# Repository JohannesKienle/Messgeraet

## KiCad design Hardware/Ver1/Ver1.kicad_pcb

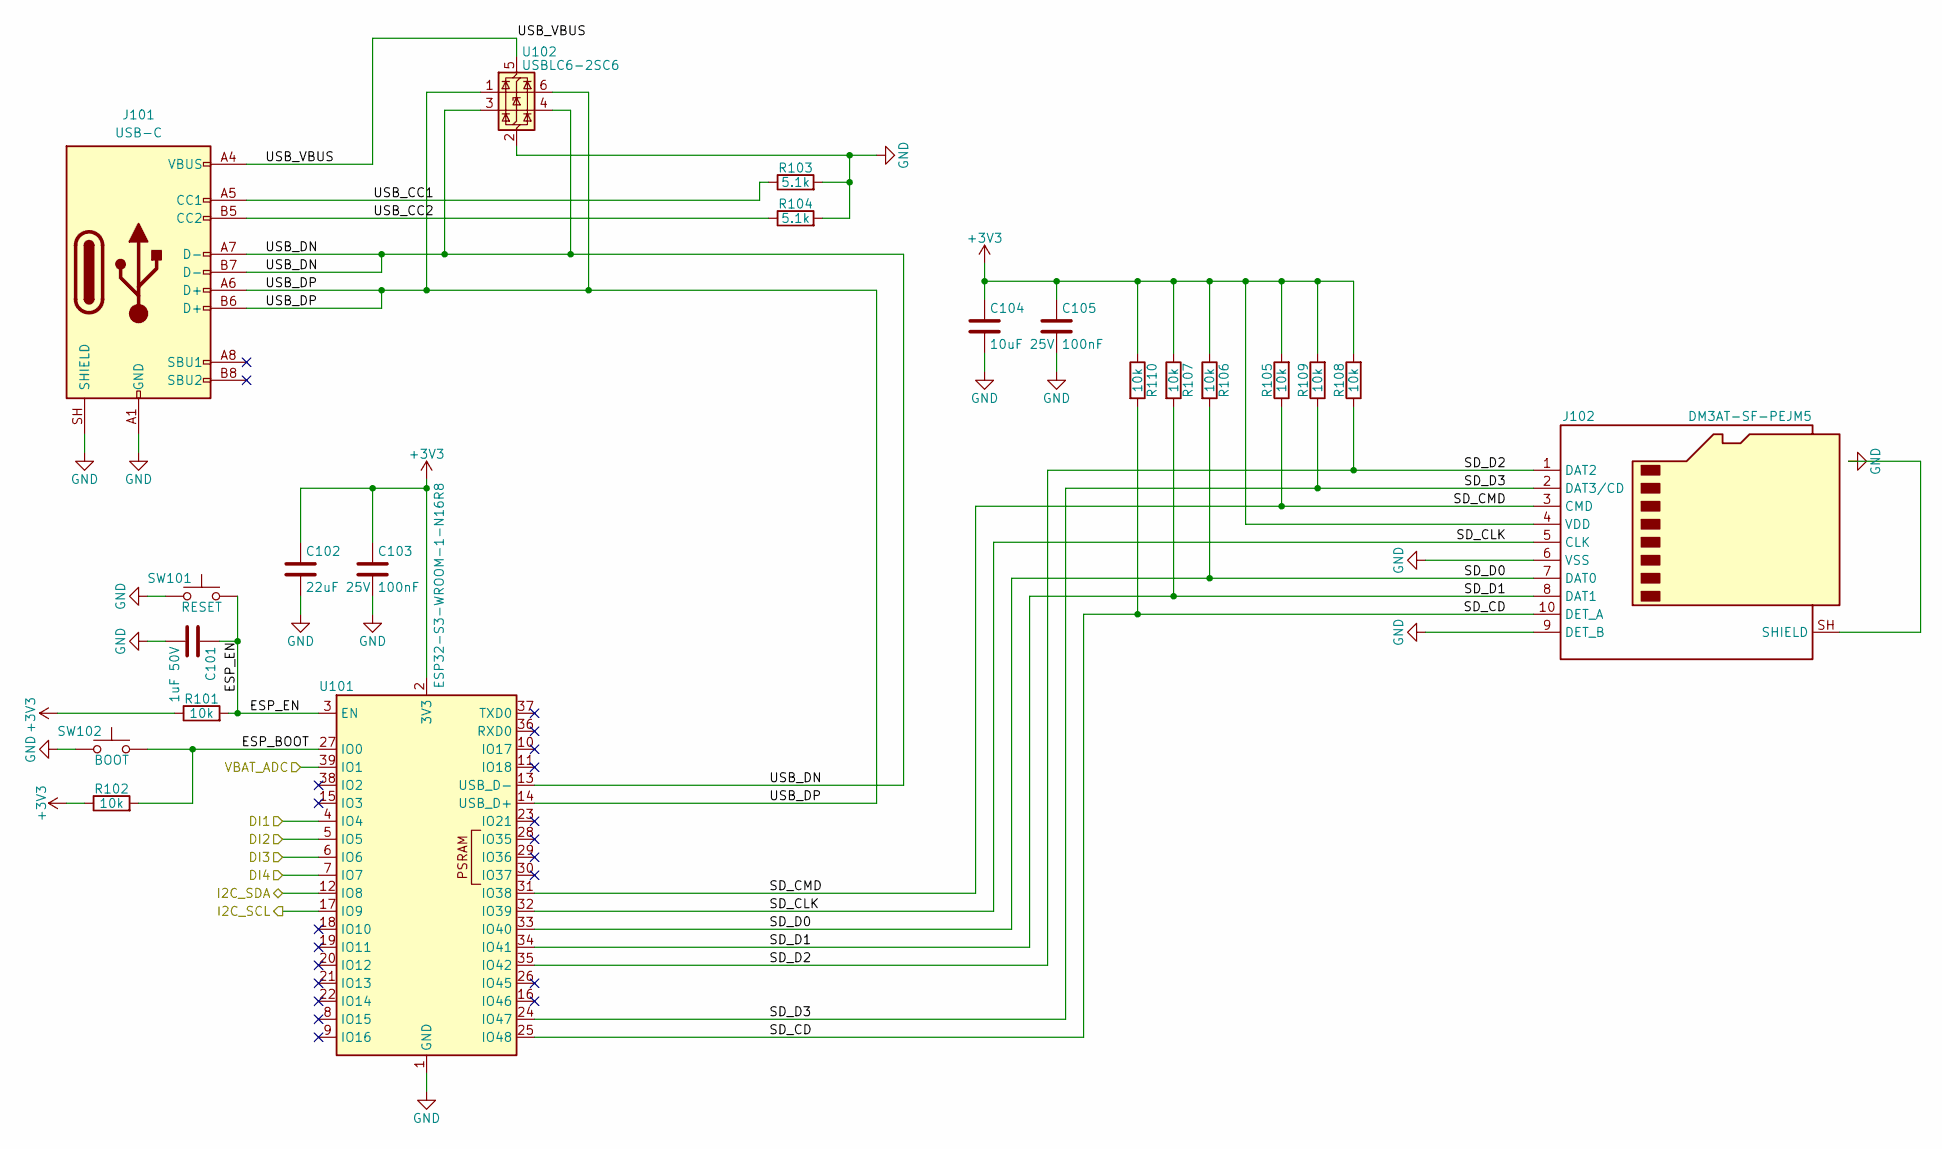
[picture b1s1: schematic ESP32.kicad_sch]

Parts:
C101: 1uF 50V; C_0805_2012Metric; MPN CL21B105KBFNNNE; LCSC C28323
C102: 22uF 25V; C_0805_2012Metric; MPN CL21A226MAQNNNE; LCSC C45783
C103, C105: 100nF; C_0805_2012Metric; MPN CC0805KRX7R9BB104; LCSC C49678
C104: 10uF 25V; C_0805_2012Metric; MPN CL21A106KAYNNNE; LCSC C15850
J101: USB-C; USB_C_Receptacle_HRO_TYPE-C-31-M-12; MPN TYPE-C-31-M-12; LCSC C165948
J102: DM3AT-SF-PEJM5; microSD_HC_Hirose_DM3AT-SF-PEJM5; MPN DM3AT-SF-PEJM5; LCSC C114218
R101, R102, R105, R106, R107, R108, R109, R110: 10k; R_0805_2012Metric; MPN 0805W8F1002T5E; LCSC C17414
R103, R104: 5.1k; R_0805_2012Metric; MPN 0805W8F5101T5E; LCSC C27834
SW101: RESET; SW_Push_1P1T_XKB_TS-1187A; MPN TS-1187A-B-A-B; LCSC C318884
SW102: BOOT; SW_Push_1P1T_XKB_TS-1187A; MPN TS-1187A-B-A-B; LCSC C318884
U101: ESP32-S3-WROOM-1-N16R8; ESP32-S3-WROOM-1; MPN ESP32-S3-WROOM-1-N16R8; LCSC C2913202
U102: USBLC6-2SC6; SOT-23-6; MPN USBLC6-2SC6; LCSC C2687116

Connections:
+3V3: C102.1, C103.1, C104.1, C105.1, J102.4 (VDD), R101.1, R102.1, R105.2, R106.1, R107.1, R108.2, R109.2, R110.1, U101.2 (3V3); also elsewhere on the board
/Analogeingänge/I2C_SCL: U101.17 (IO9); also elsewhere on the board
/Analogeingänge/I2C_SDA: U101.12 (IO8); also elsewhere on the board
/Digitaleingänge/DI1: U101.4 (IO4); also elsewhere on the board
/Digitaleingänge/DI2: U101.5 (IO5); also elsewhere on the board
/Digitaleingänge/DI3: U101.6 (IO6); also elsewhere on the board
/Digitaleingänge/DI4: U101.7 (IO7); also elsewhere on the board
/ESP32/ESP_BOOT: R102.2, SW102.1, U101.27 (IO0)
/ESP32/ESP_EN: C101.1, R101.2, SW101.1, U101.3 (EN)
/ESP32/SD_CD: J102.10 (DET_A), R110.2, U101.25 (IO48)
/ESP32/SD_CLK: J102.5 (CLK), U101.32 (IO39)
/ESP32/SD_CMD: J102.3 (CMD), R105.1, U101.31 (IO38)
/ESP32/SD_D0: J102.7 (DAT0), R106.2, U101.33 (IO40)
/ESP32/SD_D1: J102.8 (DAT1), R107.2, U101.34 (IO41)
/ESP32/SD_D2: J102.1 (DAT2), R108.1, U101.35 (IO42)
/ESP32/SD_D3: J102.2 (DAT3/CD), R109.1, U101.24 (IO47)
/ESP32/USB_CC1: J101.A5 (CC1), R103.1
/ESP32/USB_CC2: J101.B5 (CC2), R104.1
/ESP32/USB_DN: J101.A7 (D-), J101.B7 (D-), U101.13 (USB_D-), U102.3 (I/O2), U102.4 (I/O2)
/ESP32/USB_DP: J101.A6 (D+), J101.B6 (D+), U101.14 (USB_D+), U102.1 (I/O1), U102.6 (I/O1)
/ESP32/USB_VBUS: J101.A4 (VBUS), J101.A9 (VBUS), J101.B4 (VBUS), J101.B9 (VBUS), U102.5 (VBUS)
/Versorgung/VBAT_ADC: U101.39 (IO1); also elsewhere on the board

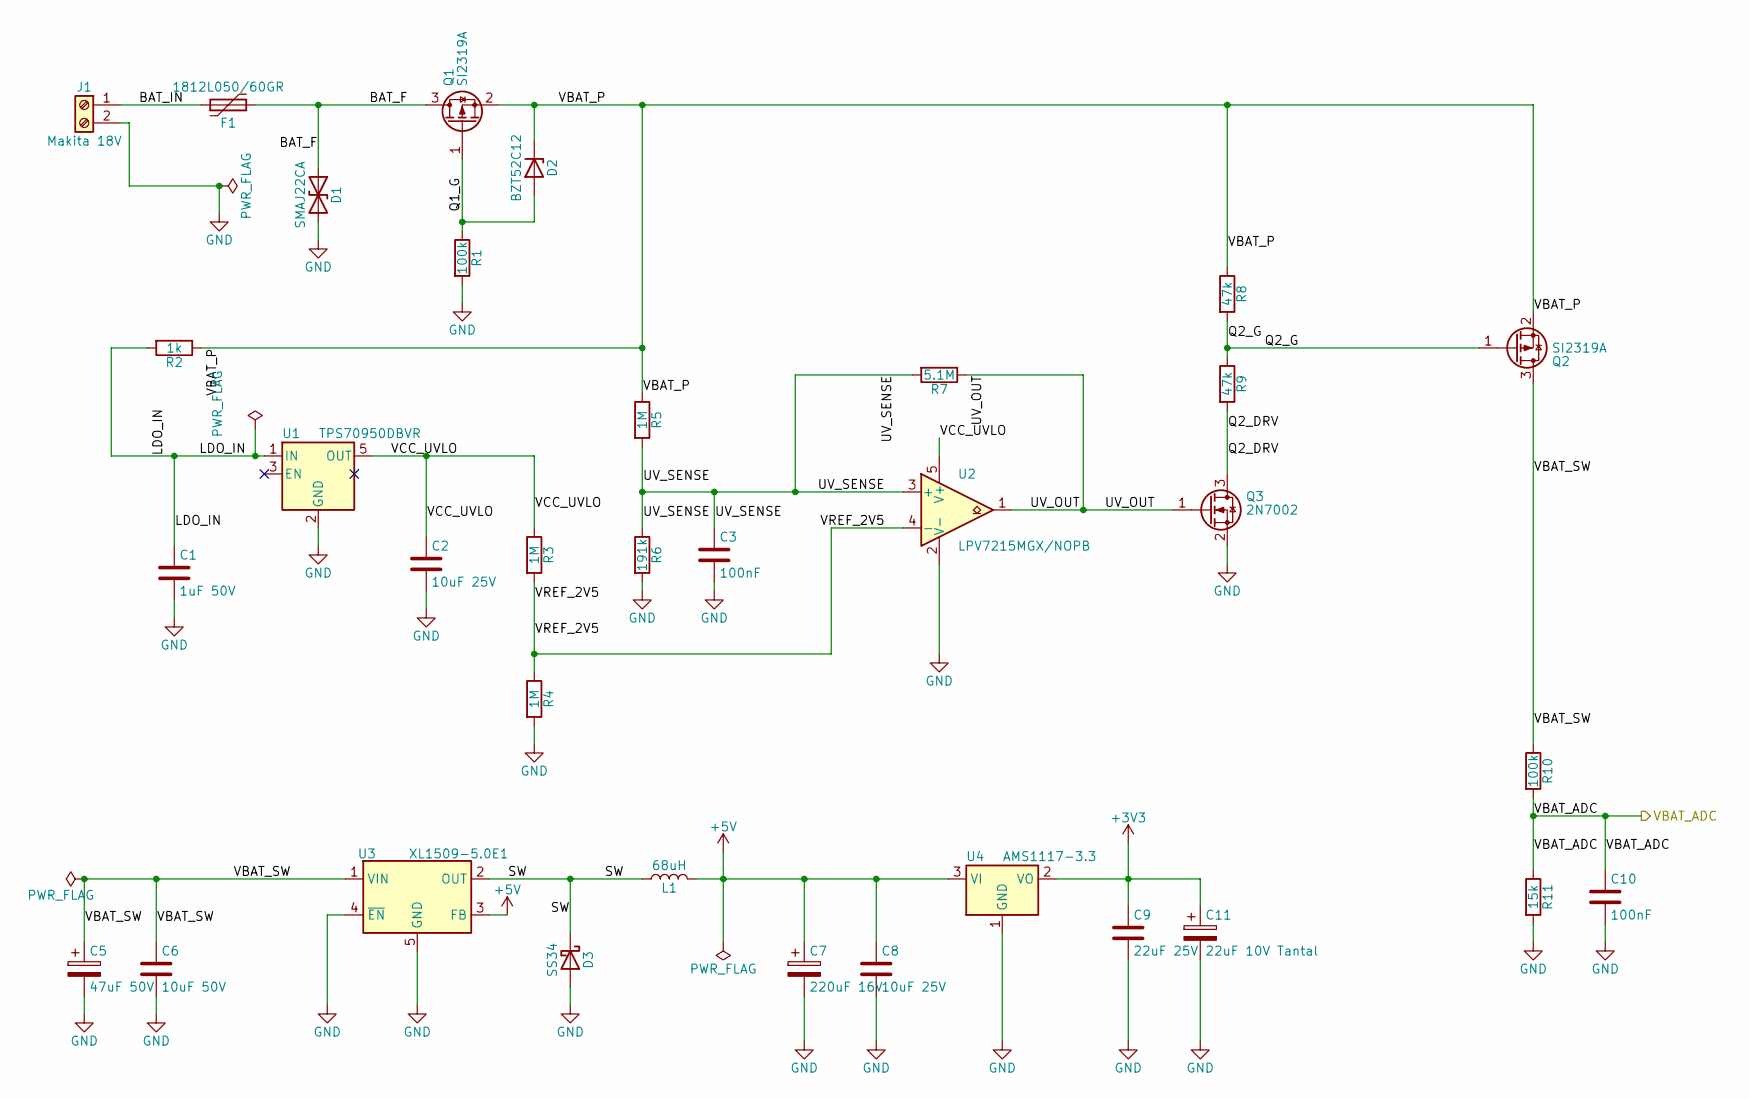
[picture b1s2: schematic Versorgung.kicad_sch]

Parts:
C1: 1uF 50V; C_0805_2012Metric; MPN CL21B105KBFNNNE; LCSC C28323
C2, C8: 10uF 25V; C_0805_2012Metric; MPN CL21A106KAYNNNE; LCSC C15850
C3, C10: 100nF; C_0805_2012Metric; MPN CC0805KRX7R9BB104; LCSC C49678
C5: 47uF 50V; CP_Radial_D6.3mm_P2.50mm; MPN ERM1HM470E11OT; LCSC C106605
C6: 10uF 50V; C_0805_2012Metric; MPN GRM21BR61H106KE43L; LCSC C440198
C7: 220uF 16V; CP_Elec_6.3x7.7; MPN EEEFK1C221P; LCSC C178534
C9: 22uF 25V; C_0805_2012Metric; MPN CL21A226MAQNNNE; LCSC C45783
C11: 22uF 10V Tantal; CP_EIA-3528-21_Kemet-B; MPN TAJB226K010RNJ; LCSC C7198
D1: SMAJ22CA; D_SMA; MPN SMAJ22CA; LCSC C113961
D2: BZT52C12; D_SOD-123; MPN BZT52C12; LCSC C43491
D3: SS34; D_SMA; MPN SS34; LCSC C8678
F1: 1812L050/60GR; Fuse_1812_4532Metric; MPN 1812L050/60GR; LCSC C19078719
J1: Makita 18V; TestPoint_2Pads_Pitch5.08mm_Drill1.3mm
L1: 68uH; L_Sunlord_SWPA8040S; MPN SWPA8040S680MT; LCSC C36418
Q1, Q2: SI2319A; SOT-23; MPN SI2319A; LCSC C545576
Q3: 2N7002; SOT-23; MPN 2N7002; LCSC C8545
R1, R10: 100k; R_0805_2012Metric; MPN 0805W8F1003T5E; LCSC C149504
R2: 1k; R_0805_2012Metric; MPN 0805W8F1001T5E; LCSC C17513
R3, R4, R5: 1M; R_0805_2012Metric; MPN 0805W8F1004T5E; LCSC C17514
R6: 191k; R_0805_2012Metric; MPN 0805W8F1913T5E; LCSC C17511
R7: 5.1M; R_0805_2012Metric; MPN 0805W8F5104T5E; LCSC C26114
R8, R9: 47k; R_0805_2012Metric; MPN 0805W8F4702T5E; LCSC C17713
R11: 15k; R_0805_2012Metric; MPN 0805W8F1502T5E; LCSC C17475
U1: TPS70950DBVR; SOT-23-5; MPN TPS70950DBVR; LCSC C96028
U2: LPV7215MGX/NOPB; SOT-353_SC-70-5; MPN LPV7215MGX/NOPB; LCSC C2878861
U3: XL1509-5.0E1; SOIC-8_3.9x4.9mm_P1.27mm; MPN XL1509-5.0E1; LCSC C61063
U4: AMS1117-3.3; SOT-223-3_TabPin2; MPN AMS1117-3.3; LCSC C6186

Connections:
+3V3: C9.1, C11.1, U4.2 (VO); also elsewhere on the board
/Versorgung/BAT_F: D1.1 (A1), F1.2, Q1.3 (D)
/Versorgung/BAT_IN: F1.1, J1.1
/Versorgung/Q1_G: D2.2 (A), Q1.1 (G), R1.1
/Versorgung/Q2_DRV: Q3.3 (D), R9.2
/Versorgung/Q2_G: Q2.1 (G), R8.2, R9.1
/Versorgung/SW: D3.1 (K), L1.1, U3.2 (OUT)
/Versorgung/UV_OUT: Q3.1 (G), R7.1, U2.1
/Versorgung/UV_SENSE: C3.1, R5.2, R6.1, R7.2, U2.3 (+)
/Versorgung/VBAT_ADC: C10.1, R10.2, R11.1; also elsewhere on the board
/Versorgung/VBAT_P: D2.1 (K), Q1.2 (S), Q2.2 (S), R2.1, R5.1, R8.1
/Versorgung/VCC_UVLO: C2.1, R3.1, U1.5 (OUT), U2.5 (V+)
/Versorgung/VREF_2V5: R3.2, R4.1, U2.4 (-)

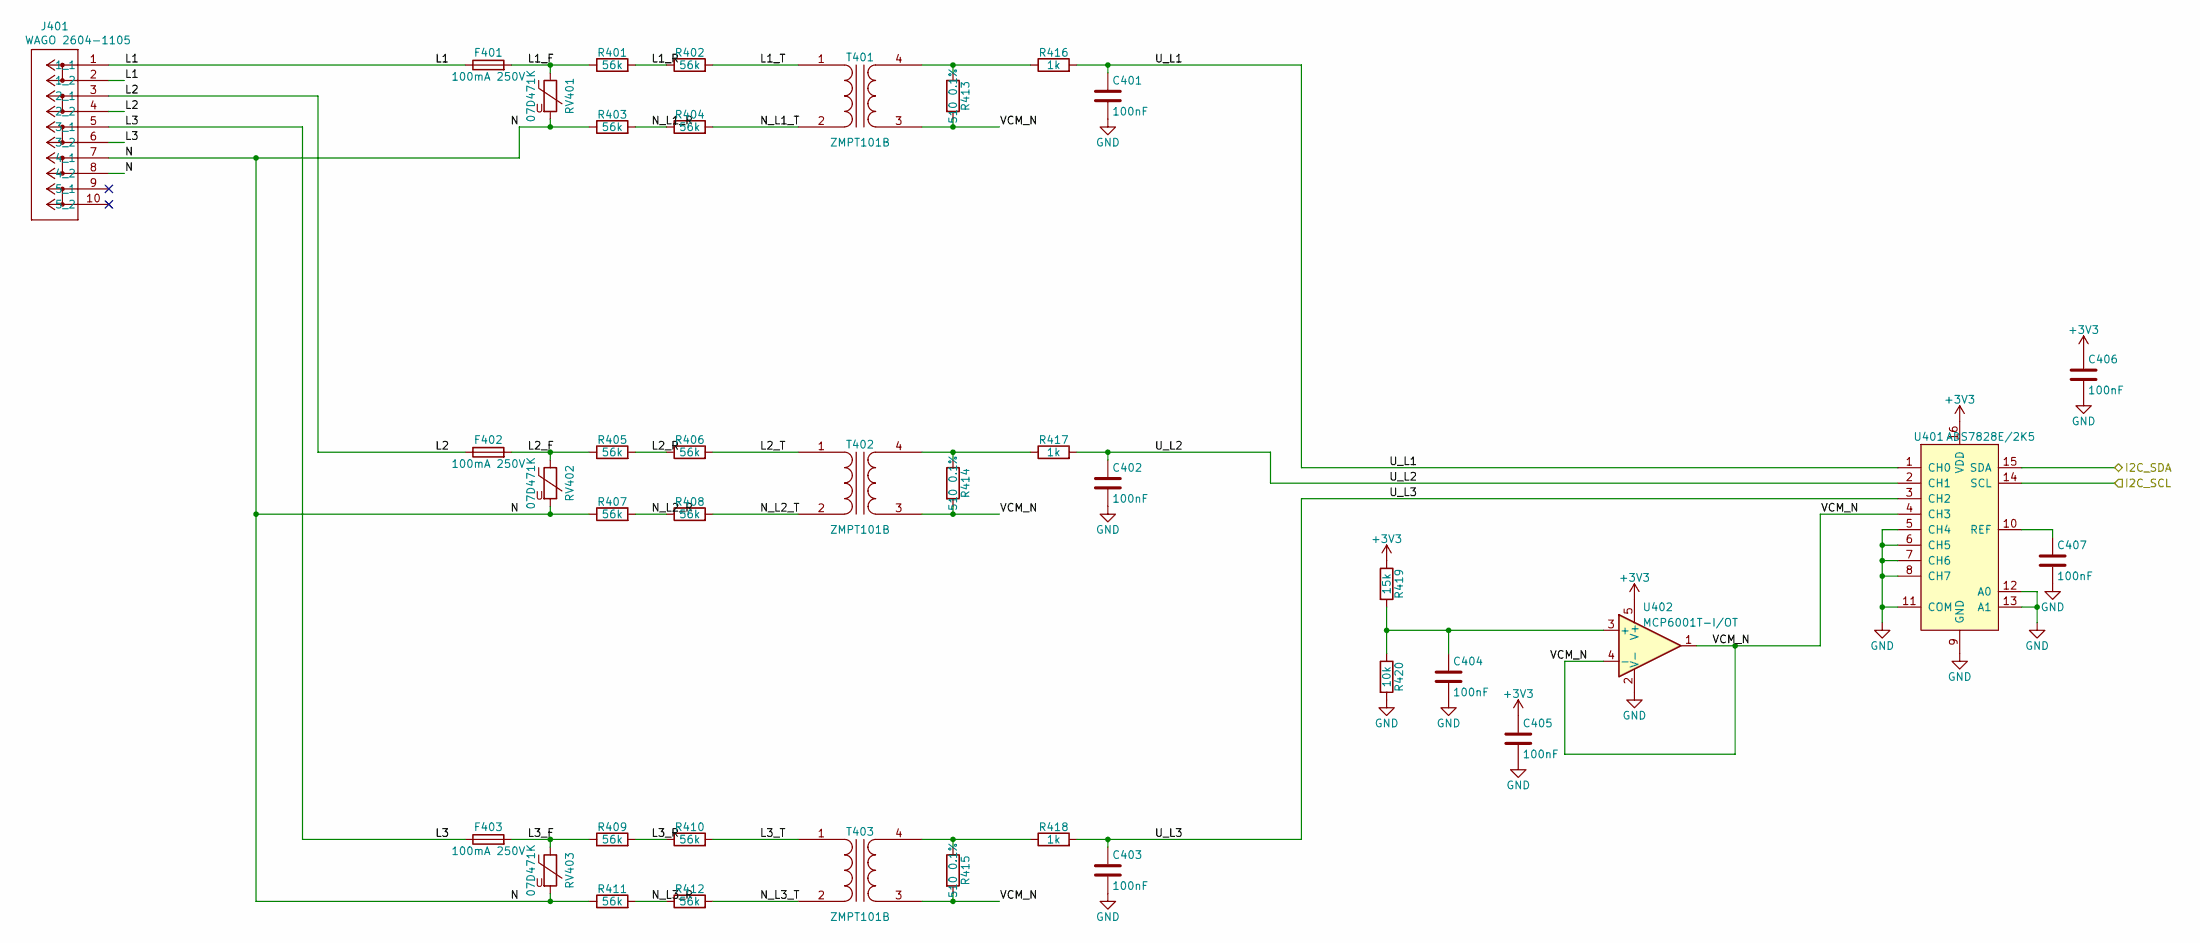
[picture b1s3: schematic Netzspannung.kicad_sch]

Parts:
C401, C402, C403, C404, C405, C406, C407: 100nF; C_0805_2012Metric; MPN CC0805KRX7R9BB104; LCSC C49678
F401, F402, F403: 100mA 250V; Fuse_2410_JDT_JFC2410; MPN JFC2410-0100FS; LCSC C48686858
J401: WAGO 2604-1105; CONN5_2604-1105_WAG; MPN WAGO 2604-1105
R401, R402, R403, R404, R405, R406, R407, R408, R409, R410, R411, R412: 56k; R_1206_3216Metric; MPN 1206W4F5602T5E; LCSC C18029
R413, R414, R415: 510 0.1%; R_0805_2012Metric; MPN RT0805BRD07510RL; LCSC C309660
R416, R417, R418: 1k; R_0805_2012Metric; MPN 0805W8F1001T5E; LCSC C17513
R419: 15k; R_0805_2012Metric; MPN 0805W8F1502T5E; LCSC C17475
R420: 10k; R_0805_2012Metric; MPN 0805W8F1002T5E; LCSC C17414
RV401, RV402, RV403: 07D471K; RV_Disc_D7mm_W3.4mm_P5mm; MPN 07D471K; LCSC C28756
T401, T402, T403: ZMPT101B; Transformer_Zeming_ZMPT101K; MPN ZMPT101B; LCSC C111858
U401: ADS7828E/2K5; TSSOP-16_4.4x5mm_P0.65mm; MPN ADS7828E/2K5; LCSC C701649
U402: MCP6001T-I/OT; SOT-23-5; MPN MCP6001T-I/OT; LCSC C116490

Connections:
+3V3: C405.1, C406.1, R419.1, U401.16 (VDD), U402.5 (V+); also elsewhere on the board
/Analogeingänge/I2C_SCL: U401.14 (SCL); also elsewhere on the board
/Analogeingänge/I2C_SDA: U401.15 (SDA); also elsewhere on the board
/Netzspannung/L1: F401.1, J401.1 (1_1), J401.2 (1_2)
/Netzspannung/L1_F: F401.2, R401.1, RV401.1
/Netzspannung/L1_R: R401.2, R402.1
/Netzspannung/L1_T: R402.2, T401.1 (AA)
/Netzspannung/L2: F402.1, J401.3 (2_1), J401.4 (2_2)
/Netzspannung/L2_F: F402.2, R405.1, RV402.1
/Netzspannung/L2_R: R405.2, R406.1
/Netzspannung/L2_T: R406.2, T402.1 (AA)
/Netzspannung/L3: F403.1, J401.5 (3_1), J401.6 (3_2)
/Netzspannung/L3_F: F403.2, R409.1, RV403.1
/Netzspannung/L3_R: R409.2, R410.1
/Netzspannung/L3_T: R410.2, T403.1 (AA)
/Netzspannung/N: J401.7 (4_1), J401.8 (4_2), R403.1, R407.1, R411.1, RV401.2, RV402.2, RV403.2
/Netzspannung/N_L1_R: R403.2, R404.1
/Netzspannung/N_L1_T: R404.2, T401.2 (AB)
/Netzspannung/N_L2_R: R407.2, R408.1
/Netzspannung/N_L2_T: R408.2, T402.2 (AB)
/Netzspannung/N_L3_R: R411.2, R412.1
/Netzspannung/N_L3_T: R412.2, T403.2 (AB)
/Netzspannung/U_L1: C401.1, R416.2, U401.1 (CH0)
/Netzspannung/U_L2: C402.1, R417.2, U401.2 (CH1)
/Netzspannung/U_L3: C403.1, R418.2, U401.3 (CH2)
/Netzspannung/VCM_N: R413.2, R414.2, R415.2, T401.3 (SA), T402.3 (SA), T403.3 (SA), U401.4 (CH3), U402.1, U402.4 (-)
unnamed: R413.1, R416.1, T401.4 (SB)
unnamed: R414.1, R417.1, T402.4 (SB)
unnamed: R415.1, R418.1, T403.4 (SB)
unnamed: C407.1, U401.10 (REF)
unnamed: C404.1, R419.2, R420.1, U402.3 (+)

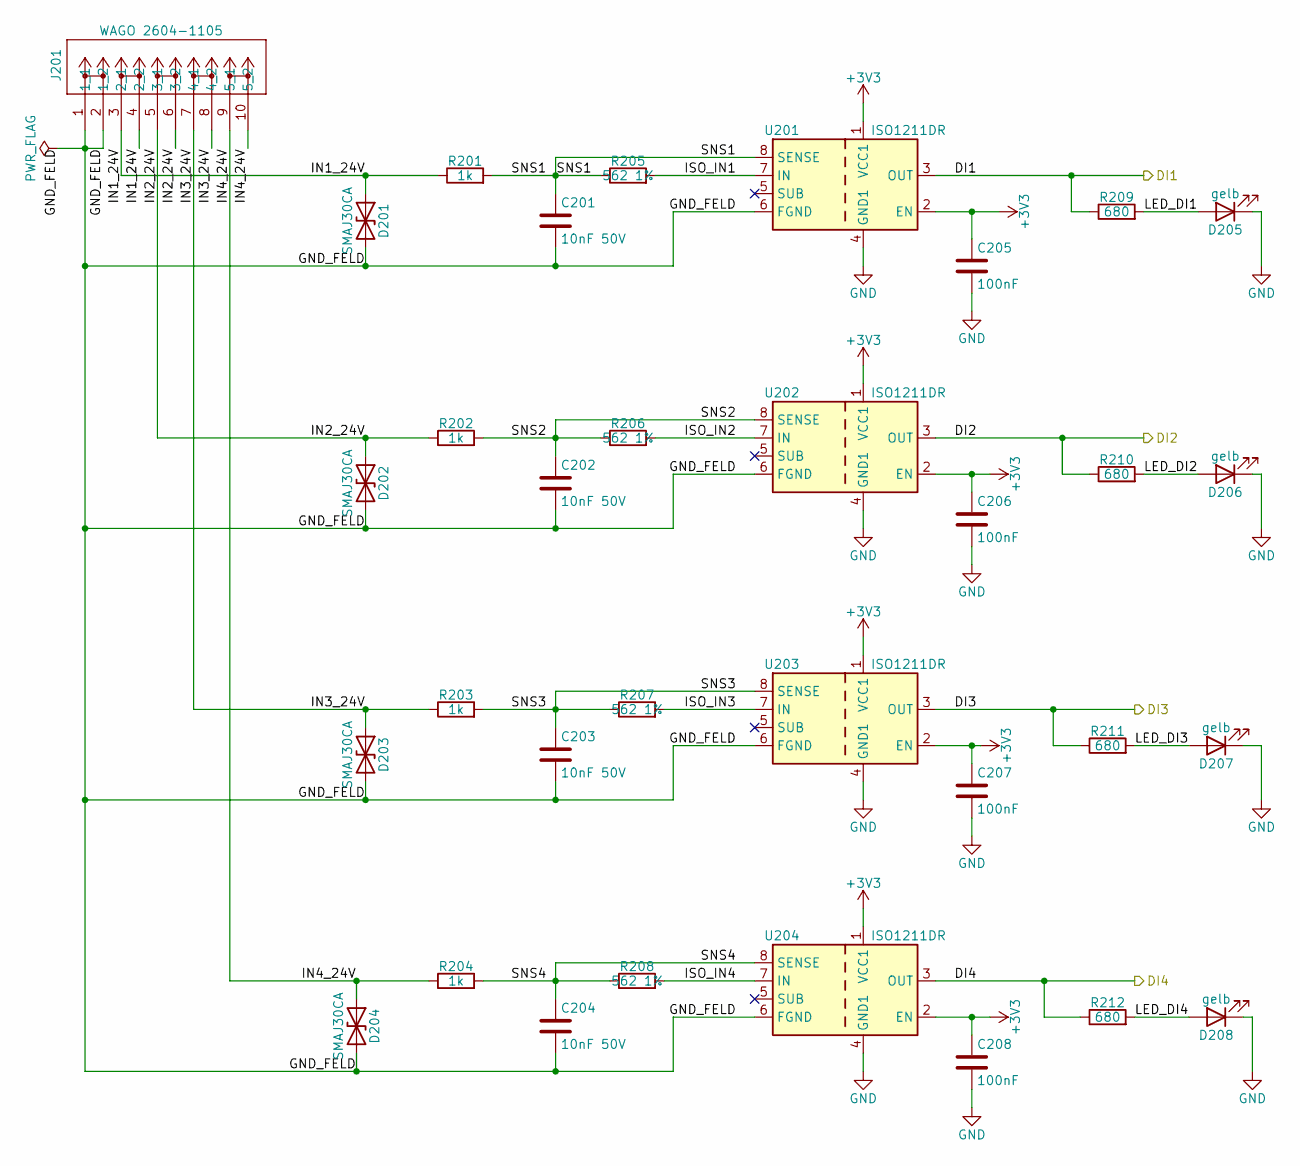
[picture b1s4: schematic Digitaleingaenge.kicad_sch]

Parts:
C201, C202, C203, C204: 10nF 50V; C_0805_2012Metric; MPN CL21B103KBANNNC; LCSC C1710
C205, C206, C207, C208: 100nF; C_0805_2012Metric; MPN CC0805KRX7R9BB104; LCSC C49678
D201, D202, D203, D204: SMAJ30CA; D_SMA; MPN SMAJ30CA; LCSC C83322
D205, D206, D207, D208: gelb; LED_0805_2012Metric; MPN KT-0805Y; LCSC C2296
J201: WAGO 2604-1105; CONN5_2604-1105_WAG; MPN WAGO 2604-1105
R201, R202, R203, R204: 1k; R_0805_2012Metric; MPN 0805W8F1001T5E; LCSC C17513
R205, R206, R207, R208: 562 1%; R_0805_2012Metric; MPN 0805W8F5620T5E; LCSC C17755
R209, R210, R211, R212: 680; R_0805_2012Metric; MPN 0805W8F6800T5E; LCSC C17798
U201, U202, U203, U204: ISO1211DR; SOIC-8_3.9x4.9mm_P1.27mm; MPN ISO1211DR; LCSC C2674102

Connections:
+3V3: C205.1, C206.1, C207.1, C208.1, U201.1 (VCC1), U201.2 (EN), U202.1 (VCC1), U202.2 (EN), U203.1 (VCC1), U203.2 (EN), U204.1 (VCC1), U204.2 (EN); also elsewhere on the board
/Digitaleingänge/DI1: R209.1, U201.3 (OUT); also elsewhere on the board
/Digitaleingänge/DI2: R210.1, U202.3 (OUT); also elsewhere on the board
/Digitaleingänge/DI3: R211.1, U203.3 (OUT); also elsewhere on the board
/Digitaleingänge/DI4: R212.1, U204.3 (OUT); also elsewhere on the board
/Digitaleingänge/GND_FELD: C201.2, C202.2, C203.2, C204.2, D201.2 (A2), D202.2 (A2), D203.2 (A2), D204.2 (A2), J201.1 (1_1), J201.2 (1_2), U201.6 (FGND), U202.6 (FGND), U203.6 (FGND), U204.6 (FGND)
/Digitaleingänge/IN1_24V: D201.1 (A1), J201.3 (2_1), J201.4 (2_2), R201.1
/Digitaleingänge/IN2_24V: D202.1 (A1), J201.5 (3_1), J201.6 (3_2), R202.1
/Digitaleingänge/IN3_24V: D203.1 (A1), J201.7 (4_1), J201.8 (4_2), R203.1
/Digitaleingänge/IN4_24V: D204.1 (A1), J201.9 (5_1), J201.10 (5_2), R204.1
/Digitaleingänge/ISO_IN1: R205.2, U201.7 (IN)
/Digitaleingänge/ISO_IN2: R206.2, U202.7 (IN)
/Digitaleingänge/ISO_IN3: R207.2, U203.7 (IN)
/Digitaleingänge/ISO_IN4: R208.2, U204.7 (IN)
/Digitaleingänge/LED_DI1: D205.2 (A), R209.2
/Digitaleingänge/LED_DI2: D206.2 (A), R210.2
/Digitaleingänge/LED_DI3: D207.2 (A), R211.2
/Digitaleingänge/LED_DI4: D208.2 (A), R212.2
/Digitaleingänge/SNS1: C201.1, R201.2, R205.1, U201.8 (SENSE)
/Digitaleingänge/SNS2: C202.1, R202.2, R206.1, U202.8 (SENSE)
/Digitaleingänge/SNS3: C203.1, R203.2, R207.1, U203.8 (SENSE)
/Digitaleingänge/SNS4: C204.1, R204.2, R208.1, U204.8 (SENSE)

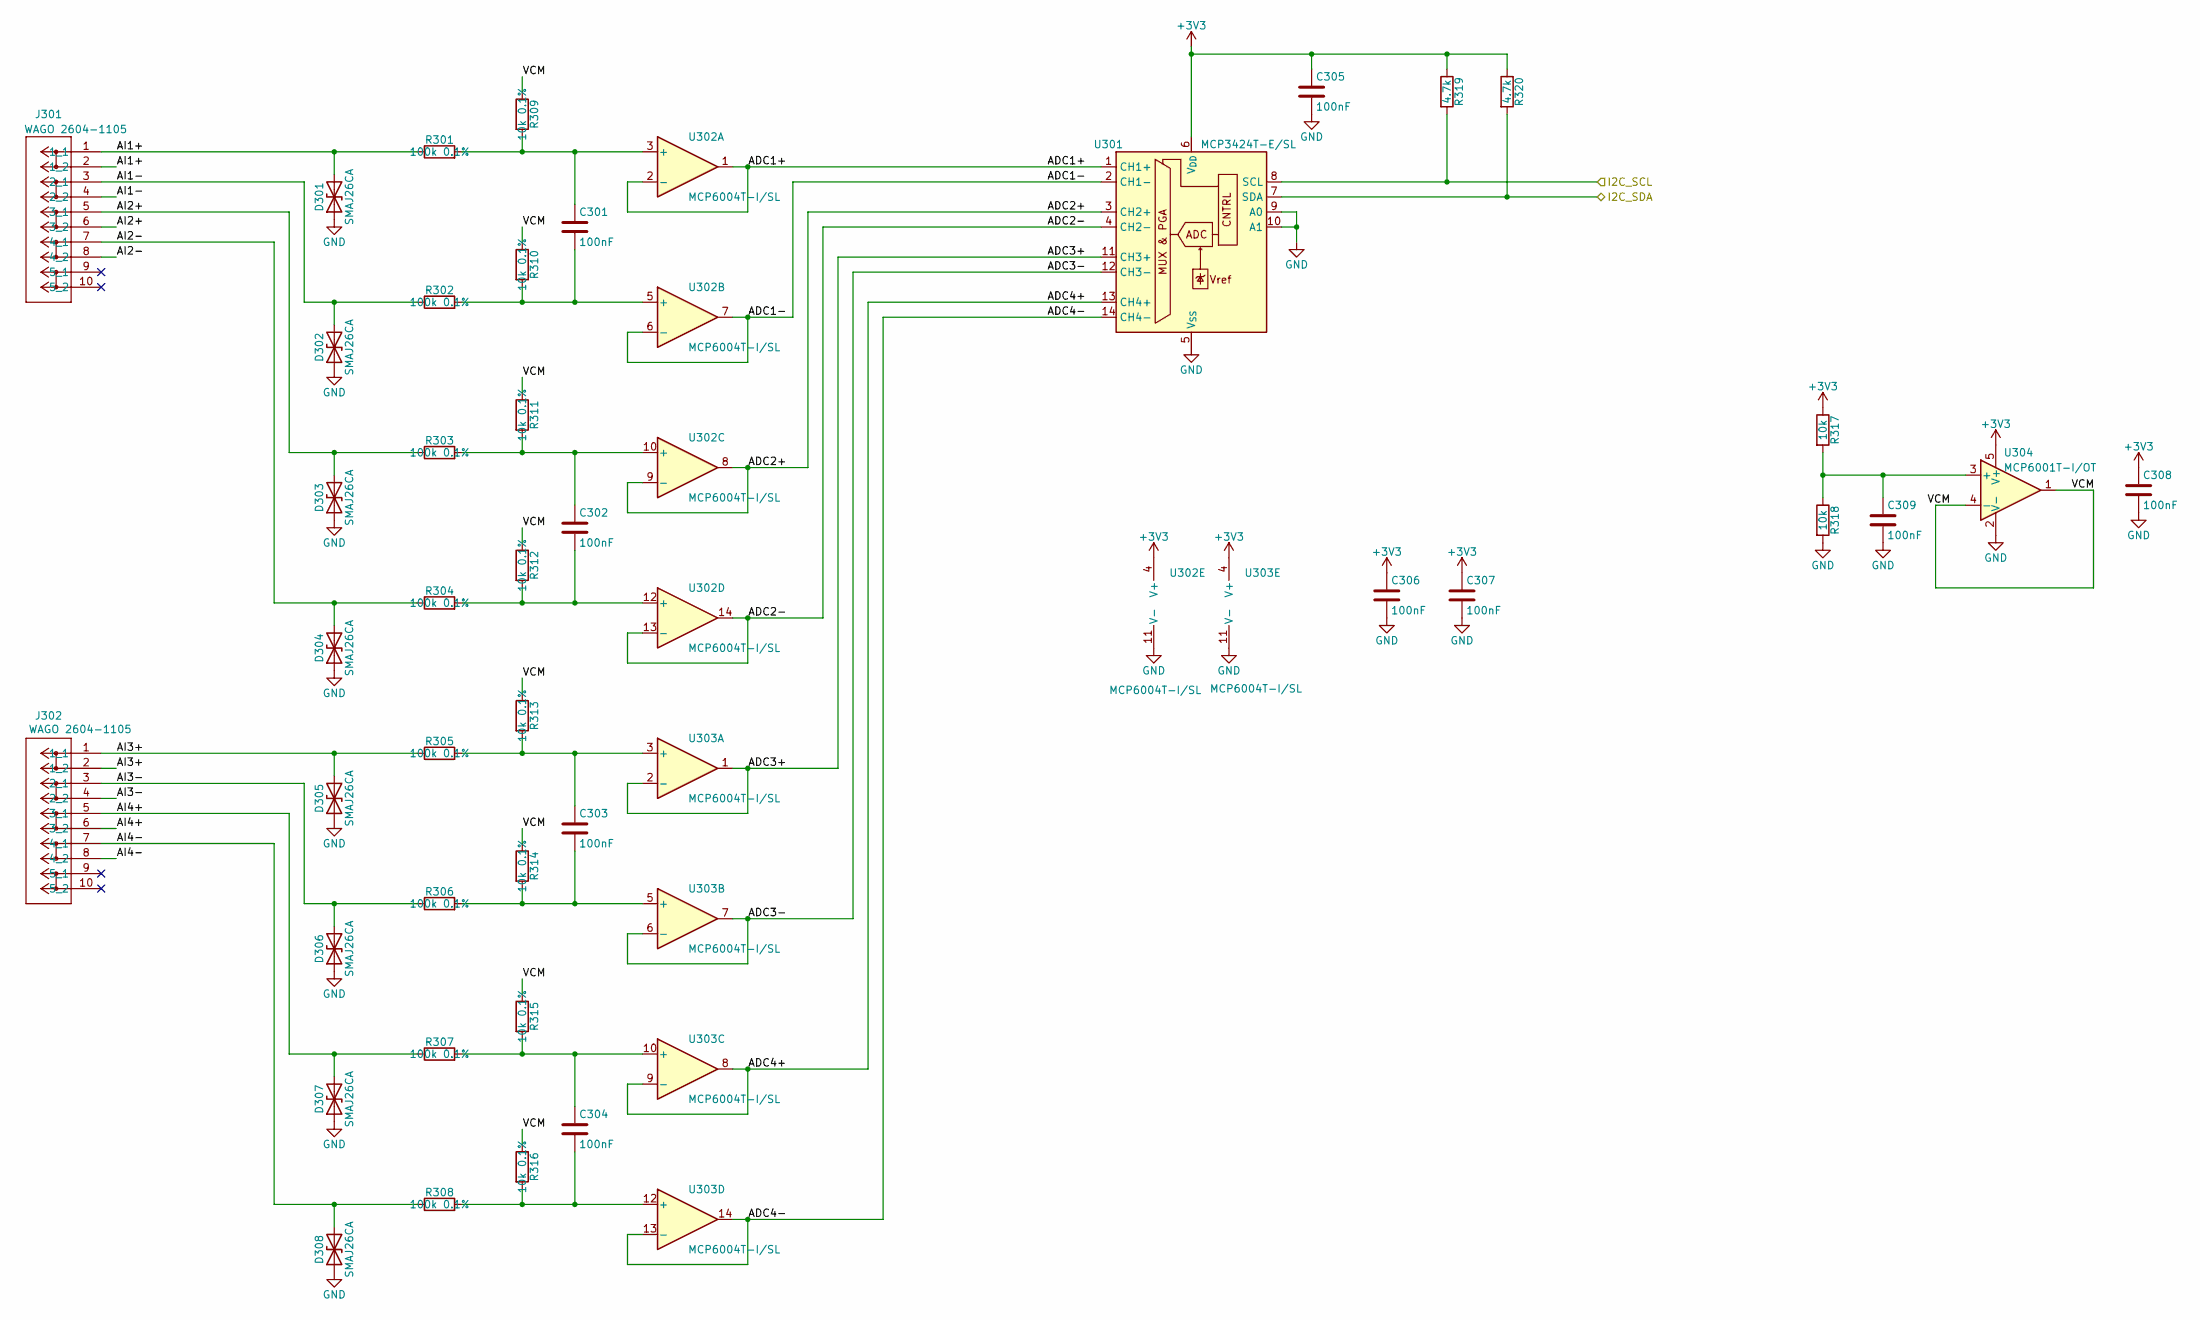
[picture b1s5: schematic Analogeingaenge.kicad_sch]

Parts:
C301, C302, C303, C304, C305, C306, C307, C308, C309: 100nF; C_0805_2012Metric; MPN CC0805KRX7R9BB104; LCSC C49678
D301, D302, D303, D304, D305, D306, D307, D308: SMAJ26CA; D_SMA; MPN SMAJ26CA; LCSC C148226
J301, J302: WAGO 2604-1105; CONN5_2604-1105_WAG; MPN WAGO 2604-1105
R301, R302, R303, R304, R305, R306, R307, R308: 100k 0.1%; R_0805_2012Metric; MPN RT0805BRD07100KL; LCSC C122537
R309, R310, R311, R312, R313, R314, R315, R316: 10k 0.1%; R_0805_2012Metric; MPN RT0805BRD0710KL; LCSC C110775
R317, R318: 10k; R_0805_2012Metric; MPN 0805W8F1002T5E; LCSC C17414
R319, R320: 4.7k; R_0805_2012Metric; MPN 0805W8F4701T5E; LCSC C17673
U301: MCP3424T-E/SL; SOIC-14_3.9x8.7mm_P1.27mm; MPN MCP3424T-E/SL; LCSC C626769
U302, U303: MCP6004T-I/SL; SOIC-14_3.9x8.7mm_P1.27mm; MPN MCP6004T-I/SL; LCSC C7378
U304: MCP6001T-I/OT; SOT-23-5; MPN MCP6001T-I/OT; LCSC C116490

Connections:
+3V3: C305.1, C306.1, C307.1, C308.1, R317.1, R319.1, R320.1, U301.6 (V_{DD}), U302.4 (V+), U303.4 (V+), U304.5 (V+); also elsewhere on the board
/Analogeingänge/ADC1+: U301.1 (CH1+), U302.1, U302.2 (-)
/Analogeingänge/ADC1-: U301.2 (CH1-), U302.6 (-), U302.7
/Analogeingänge/ADC2+: U301.3 (CH2+), U302.8, U302.9 (-)
/Analogeingänge/ADC2-: U301.4 (CH2-), U302.13 (-), U302.14
/Analogeingänge/ADC3+: U301.11 (CH3+), U303.1, U303.2 (-)
/Analogeingänge/ADC3-: U301.12 (CH3-), U303.6 (-), U303.7
/Analogeingänge/ADC4+: U301.13 (CH4+), U303.8, U303.9 (-)
/Analogeingänge/ADC4-: U301.14 (CH4-), U303.13 (-), U303.14
/Analogeingänge/AI1+: D301.2 (A2), J301.1 (1_1), J301.2 (1_2), R301.1
/Analogeingänge/AI1-: D302.2 (A2), J301.3 (2_1), J301.4 (2_2), R302.1
/Analogeingänge/AI2+: D303.2 (A2), J301.5 (3_1), J301.6 (3_2), R303.1
/Analogeingänge/AI2-: D304.2 (A2), J301.7 (4_1), J301.8 (4_2), R304.1
/Analogeingänge/AI3+: D305.2 (A2), J302.1 (1_1), J302.2 (1_2), R305.1
/Analogeingänge/AI3-: D306.2 (A2), J302.3 (2_1), J302.4 (2_2), R306.1
/Analogeingänge/AI4+: D307.2 (A2), J302.5 (3_1), J302.6 (3_2), R307.1
/Analogeingänge/AI4-: D308.2 (A2), J302.7 (4_1), J302.8 (4_2), R308.1
/Analogeingänge/I2C_SCL: R319.2, U301.8 (SCL); also elsewhere on the board
/Analogeingänge/I2C_SDA: R320.2, U301.7 (SDA); also elsewhere on the board
/Analogeingänge/VCM: R309.1, R310.1, R311.1, R312.1, R313.1, R314.1, R315.1, R316.1, U304.1, U304.4 (-)
unnamed: C301.1, R301.2, R309.2, U302.3 (+)
unnamed: C301.2, R302.2, R310.2, U302.5 (+)
unnamed: C302.1, R303.2, R311.2, U302.10 (+)
unnamed: C302.2, R304.2, R312.2, U302.12 (+)
unnamed: C303.1, R305.2, R313.2, U303.3 (+)
unnamed: C303.2, R306.2, R314.2, U303.5 (+)
unnamed: C304.1, R307.2, R315.2, U303.10 (+)
unnamed: C304.2, R308.2, R316.2, U303.12 (+)
unnamed: C309.1, R317.2, R318.1, U304.3 (+)

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
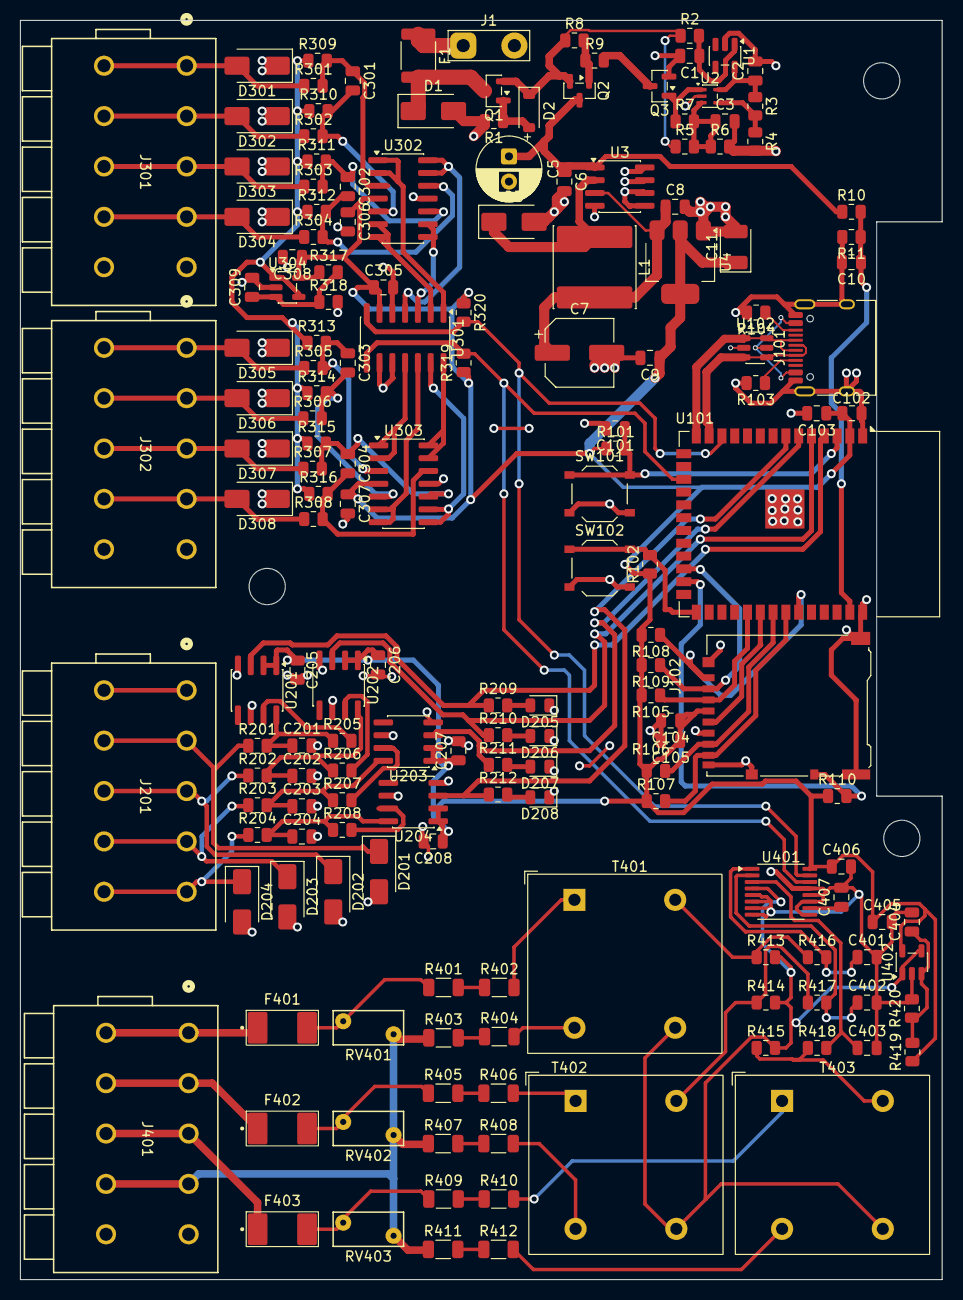
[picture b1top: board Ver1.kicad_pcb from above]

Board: 2 copper layers, 91.5 x 125.0 mm, 170 parts (0 on the bottom side), 108 nets.

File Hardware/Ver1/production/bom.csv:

Designator,Footprint,Quantity,Value,LCSC Part #
"C1, C101",0805,2,1uF 50V,C28323
"C10, C103, C105, C205, C206, C207, C208, C3, C301, C302, C303, C304, C305, C306, C307, C308, C309, C401, C402, C403, C404, C405, C406, C407",0805,24,100nF,C49678
"C102, C9",0805,2,22uF 25V,C45783
"C104, C2, C8",0805,3,10uF 25V,C15850
C11,CP_EIA-3528-21_Kemet-B,1,22uF 10V Tantal,C7198
"C201, C202, C203, C204",0805,4,10nF 50V,C1710
C5,CP_Radial_D6.3mm_P2.50mm,1,47uF 50V,C106605
C6,0805,1,10uF 50V,C440198
C7,CP_Elec_6.3x7.7,1,220uF 16V,C178534
D1,D_SMA,1,SMAJ22CA,C113961
D2,D_SOD-123,1,BZT52C12,C43491
"D201, D202, D203, D204",D_SMA,4,SMAJ30CA,C83322
"D205, D206, D207, D208",0805,4,gelb,C2296
D3,D_SMA,1,SS34,C8678
"D301, D302, D303, D304, D305, D306, D307, D308",D_SMA,8,SMAJ26CA,C148226
F1,1812,1,1812L050/60GR,C19078719
"F401, F402, F403",Fuse_2410_JDT_JFC2410,3,100mA 250V,C48686858
J1,TestPoint_2Pads_Pitch5.08mm_Drill1.3mm,1,Makita 18V,
J101,USB_C_Receptacle_HRO_TYPE-C-31-M-12,1,USB-C,C165948
J102,microSD_HC_Hirose_DM3AT-SF-PEJM5,1,DM3AT-SF-PEJM5,C114218
"J201, J301, J302, J401",CONN5_2604-1105_WAG,4,WAGO 2604-1105,WAGO 2604-1105
L1,L_Sunlord_SWPA8040S,1,68uH,C36418
"Q1, Q2",SOT-23,2,SI2319A,C545576
Q3,SOT-23,1,2N7002,C8545
"R1, R10",0805,2,100k,C149504
"R101, R102, R105, R106, R107, R108, R109, R110, R317, R318, R420",0805,11,10k,C17414
"R103, R104",0805,2,5.1k,C27834
"R11, R419",0805,2,15k,C17475
"R2, R201, R202, R203, R204, R416, R417, R418",0805,8,1k,C17513
"R205, R206, R207, R208",0805,4,562 1%,C17755
"R209, R210, R211, R212",0805,4,680,C17798
"R3, R4, R5",0805,3,1M,C17514
"R301, R302, R303, R304, R305, R306, R307, R308",0805,8,100k 0.1%,C122537
"R309, R310, R311, R312, R313, R314, R315, R316",0805,8,10k 0.1%,C110775
"R319, R320",0805,2,4.7k,C17673
"R401, R402, R403, R404, R405, R406, R407, R408, R409, R410, R411, R412",1206,12,56k,C18029
"R413, R414, R415",0805,3,510 0.1%,C309660
R6,0805,1,191k,C17511
R7,0805,1,5.1M,C26114
"R8, R9",0805,2,47k,C17713
"RV401, RV402, RV403",RV_Disc_D7mm_W3.4mm_P5mm,3,07D471K,C28756
SW101,SW_Push_1P1T_XKB_TS-1187A,1,RESET,C318884
SW102,SW_Push_1P1T_XKB_TS-1187A,1,BOOT,C318884
"T401, T402, T403",Transformer_Zeming_ZMPT101K,3,ZMPT101B,C111858
U1,SOT-23-5,1,TPS70950DBVR,C96028
U101,ESP32-S3-WROOM-1,1,ESP32-S3-WROOM-1-N16R8,C2913202
U102,SOT-23-6,1,USBLC6-2SC6,C2687116
U2,SOT-353_SC-70-5,1,LPV7215MGX/NOPB,C2878861
"U201, U202, U203, U204",SOIC-8_3.9x4.9mm_P1.27mm,4,ISO1211DR,C2674102
U3,SOIC-8_3.9x4.9mm_P1.27mm,1,XL1509-5.0E1,C61063
U301,SOIC-14_3.9x8.7mm_P1.27mm,1,MCP3424T-E/SL,C626769
"U302, U303",SOIC-14_3.9x8.7mm_P1.27mm,2,MCP6004T-I/SL,C7378
"U304, U402",SOT-23-5,2,MCP6001T-I/OT,C116490
U4,SOT-223-3_TabPin2,1,AMS1117-3.3,C6186
U401,TSSOP-16_4.4x5mm_P0.65mm,1,ADS7828E/2K5,C701649

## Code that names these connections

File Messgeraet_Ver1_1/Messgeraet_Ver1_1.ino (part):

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
// ---------- Pinbelegung (Schaltplan Ver1) ----------
const uint8_t PIN_DI[4]    = { 4, 5, 6, 7 };   // DI1..DI4, ISO1211 OUT
const uint8_t PIN_I2C_SDA  = 8;
const uint8_t PIN_I2C_SCL  = 9;
const uint8_t PIN_VBAT_ADC = 1;
const uint8_t PIN_SD_CLK   = 39;
const uint8_t PIN_SD_CMD   = 38;
const uint8_t PIN_SD_D0    = 40;
const uint8_t PIN_SD_D1    = 41;
const uint8_t PIN_SD_D2    = 42;
const uint8_t PIN_SD_D3    = 47;
const uint8_t PIN_SD_CD    = 48;

// ---------- Analogeingaenge AI1..AI4 (MCP3424) ----------
const uint8_t MCP3424_ADDR = 0x68;             // Adr0 = Adr1 = GND
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
  for (;;) {
    // ---- Kartenerkennung (entprellt) ----
    bool raw = SD_USE_CARD_DETECT ? (digitalRead(PIN_SD_CD) == (SD_CD_ACTIVE_LOW ? LOW : HIGH)) : true;
    if (raw != cdStable) {
      if (++cdCount >= 4) { cdStable = raw; cdCount = 0; }
    } else {
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  Serial.printf("AI-Nullabgleich: %.1f  %.1f  %.1f  %.1f mV\n", aiZeroV[0] * 1000.0, aiZeroV[1] * 1000.0, aiZeroV[2] * 1000.0, aiZeroV[3] * 1000.0);
  Serial.printf("Netz: L1 %.1f  L2 %.1f  L3 %.1f V (%u Abtastungen je %lu ms)\n", (double)acVolts[0], (double)acVolts[1],
                (double)acVolts[2], acWindowSamples, (unsigned long)AC_WINDOW_MS);
  Serial.printf("SD: Erkennung IO48=%d, %s, %lu MB frei von %lu MB, Fehlercode %u\n", digitalRead(PIN_SD_CD),
                sdMounted ? "bereit" : (sdPresent ? "nicht lesbar" : "keine Karte"),
                (unsigned long)st.freeMB, (unsigned long)st.totalMB, st.sdError);
  Serial.printf("Langzeitmessung: %s, Datei %s, %lu Zeilen, %lu kB, Intervall %lu ms, verloren %lu\n",
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  if (millis() - last < 250) return;
  last = millis();

  float v = analogReadMilliVolts(PIN_VBAT_ADC) * 0.001f * BAT_DIVIDER * BAT_CAL;
  filt = (filt == 0) ? v : filt + 0.2f * (v - filt);
  batteryMv = (uint16_t)(filt * 1000.0f);

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#endif

  for (uint8_t i = 0; i < 4; i++) pinMode(PIN_DI[i], INPUT);   // ISO1211 treibt aktiv HIGH/LOW
  pinMode(PIN_SD_CD, INPUT_PULLUP);                            // zusaetzlich zu R110 auf der Platine
  analogSetPinAttenuation(PIN_VBAT_ADC, ADC_11db);             // Messbereich bis ca. 3,1 V am Pin

  prefs.begin("messgeraet", false);
  if (prefs.getBytesLength("aiZero") == 4 * sizeof(float)) {   // gespeicherten Nullabgleich laden
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  sdCmdQueue  = xQueueCreate(6, sizeof(SdCmd));
  bleJobQueue = xQueueCreate(8, sizeof(BleJob));

  Wire.begin(PIN_I2C_SDA, PIN_I2C_SCL, 400000);   // I2C Fast Mode
  Wire.setTimeOut(20);                            // haengt der Bus, abbrechen statt lange warten

  SD_MMC.setPins(PIN_SD_CLK, PIN_SD_CMD, PIN_SD_D0, PIN_SD_D1, PIN_SD_D2, PIN_SD_D3);

  // ---------- BLE ----------
  NimBLEDevice::init(BLE_DEVICE_NAME);
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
